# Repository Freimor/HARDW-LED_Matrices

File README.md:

## Stack of different led modular matrices.
I make modular matrices on different LEDs in the same form factor. Trying to make the smallest 8x8 matrix.

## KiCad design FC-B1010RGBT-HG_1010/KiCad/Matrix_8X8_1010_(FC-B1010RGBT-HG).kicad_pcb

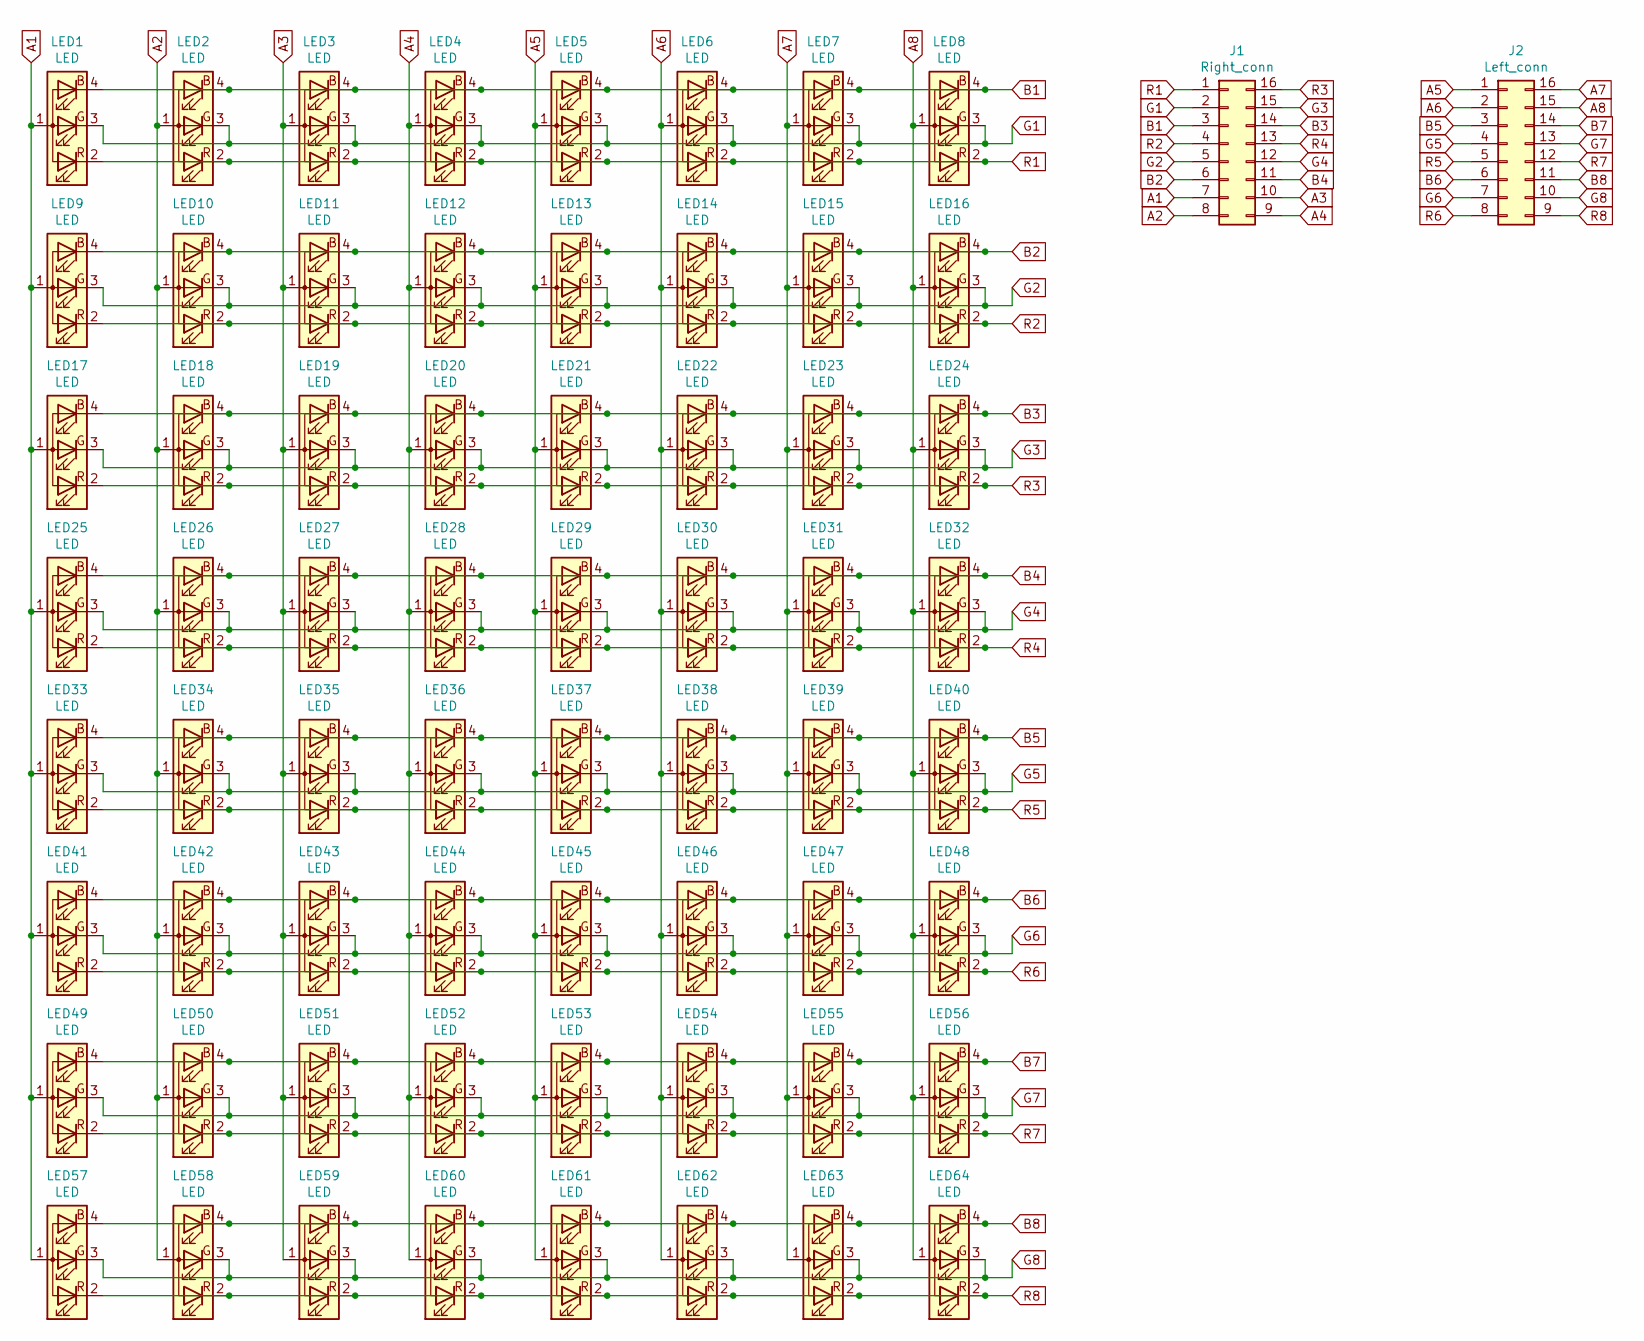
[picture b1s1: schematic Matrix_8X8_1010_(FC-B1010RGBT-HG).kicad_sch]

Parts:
J1: Right_conn; Conn_Molex_5050701642(SlimStack_16pin_header)
J2: Left_conn; Conn_Molex_5050701642(SlimStack_16pin_header)
LED1, LED2, LED3, LED4, LED5, LED6, LED7, LED8, LED9, LED10, LED11, LED12, LED13, LED14, LED15, LED16, LED17, LED18, LED19, LED20, LED21, LED22, LED23, LED24, LED25, LED26, LED27, LED28, LED29, LED30, LED31, LED32, LED33, LED34, LED35, LED36, LED37, LED38, LED39, LED40, LED41, LED42, LED43, LED44, LED45, LED46, LED47, LED48, LED49, LED50, LED51, LED52, LED53, LED54, LED55, LED56, LED57, LED58, LED59, LED60, LED61, LED62, LED63, LED64: LED; LED_RGB_FC-B1010RGBT-HG

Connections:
A1: J1.7, LED1.1 (A), LED9.1 (A), LED17.1 (A), LED25.1 (A), LED33.1 (A), LED41.1 (A), LED49.1 (A), LED57.1 (A)
A2: J1.8, LED2.1 (A), LED10.1 (A), LED18.1 (A), LED26.1 (A), LED34.1 (A), LED42.1 (A), LED50.1 (A), LED58.1 (A)
A3: J1.10, LED3.1 (A), LED11.1 (A), LED19.1 (A), LED27.1 (A), LED35.1 (A), LED43.1 (A), LED51.1 (A), LED59.1 (A)
A4: J1.9, LED4.1 (A), LED12.1 (A), LED20.1 (A), LED28.1 (A), LED36.1 (A), LED44.1 (A), LED52.1 (A), LED60.1 (A)
A5: J2.1, LED5.1 (A), LED13.1 (A), LED21.1 (A), LED29.1 (A), LED37.1 (A), LED45.1 (A), LED53.1 (A), LED61.1 (A)
A6: J2.2, LED6.1 (A), LED14.1 (A), LED22.1 (A), LED30.1 (A), LED38.1 (A), LED46.1 (A), LED54.1 (A), LED62.1 (A)
A7: J2.16, LED7.1 (A), LED15.1 (A), LED23.1 (A), LED31.1 (A), LED39.1 (A), LED47.1 (A), LED55.1 (A), LED63.1 (A)
A8: J2.15, LED8.1 (A), LED16.1 (A), LED24.1 (A), LED32.1 (A), LED40.1 (A), LED48.1 (A), LED56.1 (A), LED64.1 (A)
B1: J1.3, LED1.4 (BK), LED2.4 (BK), LED3.4 (BK), LED4.4 (BK), LED5.4 (BK), LED6.4 (BK), LED7.4 (BK), LED8.4 (BK)
B2: J1.6, LED9.4 (BK), LED10.4 (BK), LED11.4 (BK), LED12.4 (BK), LED13.4 (BK), LED14.4 (BK), LED15.4 (BK), LED16.4 (BK)
B3: J1.14, LED17.4 (BK), LED18.4 (BK), LED19.4 (BK), LED20.4 (BK), LED21.4 (BK), LED22.4 (BK), LED23.4 (BK), LED24.4 (BK)
B4: J1.11, LED25.4 (BK), LED26.4 (BK), LED27.4 (BK), LED28.4 (BK), LED29.4 (BK), LED30.4 (BK), LED31.4 (BK), LED32.4 (BK)
B5: J2.3, LED33.4 (BK), LED34.4 (BK), LED35.4 (BK), LED36.4 (BK), LED37.4 (BK), LED38.4 (BK), LED39.4 (BK), LED40.4 (BK)
B6: J2.6, LED41.4 (BK), LED42.4 (BK), LED43.4 (BK), LED44.4 (BK), LED45.4 (BK), LED46.4 (BK), LED47.4 (BK), LED48.4 (BK)
B7: J2.14, LED49.4 (BK), LED50.4 (BK), LED51.4 (BK), LED52.4 (BK), LED53.4 (BK), LED54.4 (BK), LED55.4 (BK), LED56.4 (BK)
B8: J2.11, LED57.4 (BK), LED58.4 (BK), LED59.4 (BK), LED60.4 (BK), LED61.4 (BK), LED62.4 (BK), LED63.4 (BK), LED64.4 (BK)
G1: J1.2, LED1.3 (GK), LED2.3 (GK), LED3.3 (GK), LED4.3 (GK), LED5.3 (GK), LED6.3 (GK), LED7.3 (GK), LED8.3 (GK)
G2: J1.5, LED9.3 (GK), LED10.3 (GK), LED11.3 (GK), LED12.3 (GK), LED13.3 (GK), LED14.3 (GK), LED15.3 (GK), LED16.3 (GK)
G3: J1.15, LED17.3 (GK), LED18.3 (GK), LED19.3 (GK), LED20.3 (GK), LED21.3 (GK), LED22.3 (GK), LED23.3 (GK), LED24.3 (GK)
G4: J1.12, LED25.3 (GK), LED26.3 (GK), LED27.3 (GK), LED28.3 (GK), LED29.3 (GK), LED30.3 (GK), LED31.3 (GK), LED32.3 (GK)
G5: J2.4, LED33.3 (GK), LED34.3 (GK), LED35.3 (GK), LED36.3 (GK), LED37.3 (GK), LED38.3 (GK), LED39.3 (GK), LED40.3 (GK)
G6: J2.7, LED41.3 (GK), LED42.3 (GK), LED43.3 (GK), LED44.3 (GK), LED45.3 (GK), LED46.3 (GK), LED47.3 (GK), LED48.3 (GK)
G7: J2.13, LED49.3 (GK), LED50.3 (GK), LED51.3 (GK), LED52.3 (GK), LED53.3 (GK), LED54.3 (GK), LED55.3 (GK), LED56.3 (GK)
G8: J2.10, LED57.3 (GK), LED58.3 (GK), LED59.3 (GK), LED60.3 (GK), LED61.3 (GK), LED62.3 (GK), LED63.3 (GK), LED64.3 (GK)
R1: J1.1, LED1.2 (RK), LED2.2 (RK), LED3.2 (RK), LED4.2 (RK), LED5.2 (RK), LED6.2 (RK), LED7.2 (RK), LED8.2 (RK)
R2: J1.4, LED9.2 (RK), LED10.2 (RK), LED11.2 (RK), LED12.2 (RK), LED13.2 (RK), LED14.2 (RK), LED15.2 (RK), LED16.2 (RK)
R3: J1.16, LED17.2 (RK), LED18.2 (RK), LED19.2 (RK), LED20.2 (RK), LED21.2 (RK), LED22.2 (RK), LED23.2 (RK), LED24.2 (RK)
R4: J1.13, LED25.2 (RK), LED26.2 (RK), LED27.2 (RK), LED28.2 (RK), LED29.2 (RK), LED30.2 (RK), LED31.2 (RK), LED32.2 (RK)
R5: J2.5, LED33.2 (RK), LED34.2 (RK), LED35.2 (RK), LED36.2 (RK), LED37.2 (RK), LED38.2 (RK), LED39.2 (RK), LED40.2 (RK)
R6: J2.8, LED41.2 (RK), LED42.2 (RK), LED43.2 (RK), LED44.2 (RK), LED45.2 (RK), LED46.2 (RK), LED47.2 (RK), LED48.2 (RK)
R7: J2.12, LED49.2 (RK), LED50.2 (RK), LED51.2 (RK), LED52.2 (RK), LED53.2 (RK), LED54.2 (RK), LED55.2 (RK), LED56.2 (RK)
R8: J2.9, LED57.2 (RK), LED58.2 (RK), LED59.2 (RK), LED60.2 (RK), LED61.2 (RK), LED62.2 (RK), LED63.2 (RK), LED64.2 (RK)

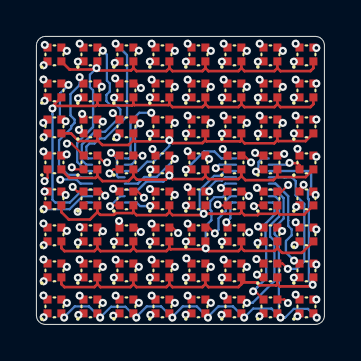
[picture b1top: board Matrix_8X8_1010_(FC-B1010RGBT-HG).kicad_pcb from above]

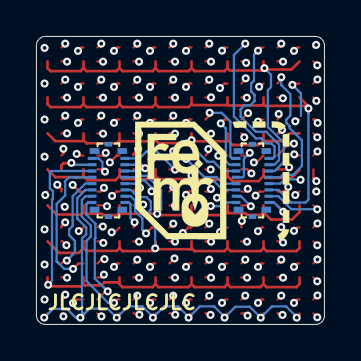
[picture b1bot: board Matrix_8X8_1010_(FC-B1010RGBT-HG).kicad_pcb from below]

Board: 4 copper layers, 16.0 x 16.0 mm, 67 parts (2 on the bottom side), 32 nets.

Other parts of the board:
Ref**: Val**; drawing

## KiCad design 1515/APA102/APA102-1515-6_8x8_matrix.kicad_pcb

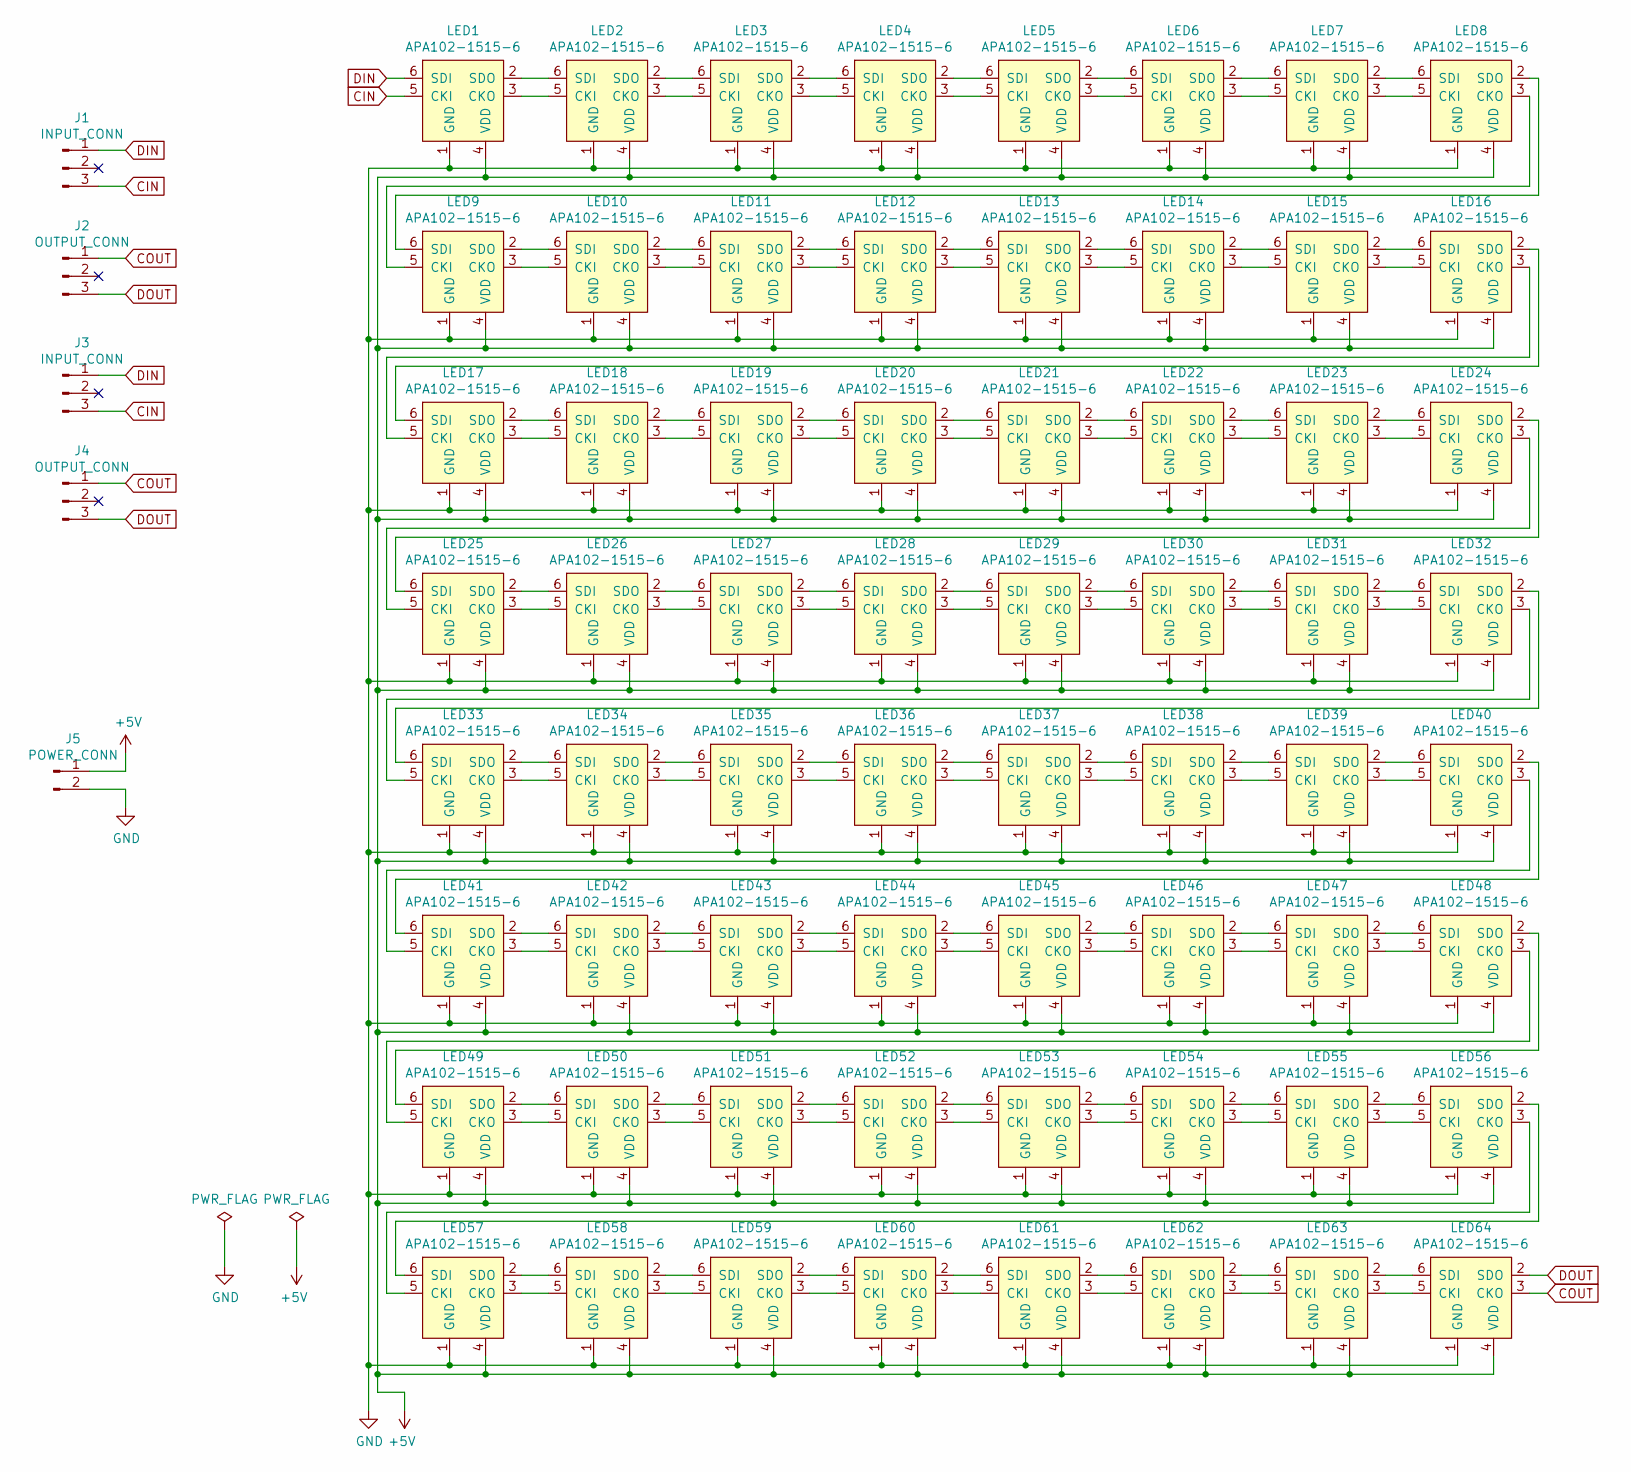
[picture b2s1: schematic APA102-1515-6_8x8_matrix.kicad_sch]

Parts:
J1, J3: INPUT_CONN; Conn_Hirose_DF59-3S-2V
J2, J4: OUTPUT_CONN; Conn_Hirose_DF59-3S-2V
J5: POWER_CONN; Conn_Molex_2026560021(Pico-EZmate_Slim)
LED1, LED2, LED3, LED4, LED5, LED6, LED7, LED8, LED9, LED10, LED11, LED12, LED13, LED14, LED15, LED16, LED17, LED18, LED19, LED20, LED21, LED22, LED23, LED24, LED25, LED26, LED27, LED28, LED29, LED30, LED31, LED32, LED33, LED34, LED35, LED36, LED37, LED38, LED39, LED40, LED41, LED42, LED43, LED44, LED45, LED46, LED47, LED48, LED49, LED50, LED51, LED52, LED53, LED54, LED55, LED56, LED57, LED58, LED59, LED60, LED61, LED62, LED63, LED64: APA102-1515-6

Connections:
+5V: J5.1, LED1.4 (VDD), LED2.4 (VDD), LED3.4 (VDD), LED4.4 (VDD), LED5.4 (VDD), LED6.4 (VDD), LED7.4 (VDD), LED8.4 (VDD), LED9.4 (VDD), LED10.4 (VDD), LED11.4 (VDD), LED12.4 (VDD), LED13.4 (VDD), LED14.4 (VDD), LED15.4 (VDD), LED16.4 (VDD), LED17.4 (VDD), LED18.4 (VDD), LED19.4 (VDD), LED20.4 (VDD), LED21.4 (VDD), LED22.4 (VDD), LED23.4 (VDD), LED24.4 (VDD), LED25.4 (VDD), LED26.4 (VDD), LED27.4 (VDD), LED28.4 (VDD), LED29.4 (VDD), LED30.4 (VDD), LED31.4 (VDD), LED32.4 (VDD), LED33.4 (VDD), LED34.4 (VDD), LED35.4 (VDD), LED36.4 (VDD), LED37.4 (VDD), LED38.4 (VDD), LED39.4 (VDD), LED40.4 (VDD), LED41.4 (VDD), LED42.4 (VDD), LED43.4 (VDD), LED44.4 (VDD), LED45.4 (VDD), LED46.4 (VDD), LED47.4 (VDD), LED48.4 (VDD), LED49.4 (VDD), LED50.4 (VDD), LED51.4 (VDD), LED52.4 (VDD), LED53.4 (VDD), LED54.4 (VDD), LED55.4 (VDD), LED56.4 (VDD), LED57.4 (VDD), LED58.4 (VDD), LED59.4 (VDD), LED60.4 (VDD), LED61.4 (VDD), LED62.4 (VDD), LED63.4 (VDD), LED64.4 (VDD)
CIN: J1.3, J3.3, LED1.5 (CKI)
COUT: J2.1, J4.1, LED64.3 (CKO)
DIN: J1.1, J3.1, LED1.6 (SDI)
DOUT: J2.3, J4.3, LED64.2 (SDO)
GND: J5.2, LED1.1 (GND), LED2.1 (GND), LED3.1 (GND), LED4.1 (GND), LED5.1 (GND), LED6.1 (GND), LED7.1 (GND), LED8.1 (GND), LED9.1 (GND), LED10.1 (GND), LED11.1 (GND), LED12.1 (GND), LED13.1 (GND), LED14.1 (GND), LED15.1 (GND), LED16.1 (GND), LED17.1 (GND), LED18.1 (GND), LED19.1 (GND), LED20.1 (GND), LED21.1 (GND), LED22.1 (GND), LED23.1 (GND), LED24.1 (GND), LED25.1 (GND), LED26.1 (GND), LED27.1 (GND), LED28.1 (GND), LED29.1 (GND), LED30.1 (GND), LED31.1 (GND), LED32.1 (GND), LED33.1 (GND), LED34.1 (GND), LED35.1 (GND), LED36.1 (GND), LED37.1 (GND), LED38.1 (GND), LED39.1 (GND), LED40.1 (GND), LED41.1 (GND), LED42.1 (GND), LED43.1 (GND), LED44.1 (GND), LED45.1 (GND), LED46.1 (GND), LED47.1 (GND), LED48.1 (GND), LED49.1 (GND), LED50.1 (GND), LED51.1 (GND), LED52.1 (GND), LED53.1 (GND), LED54.1 (GND), LED55.1 (GND), LED56.1 (GND), LED57.1 (GND), LED58.1 (GND), LED59.1 (GND), LED60.1 (GND), LED61.1 (GND), LED62.1 (GND), LED63.1 (GND), LED64.1 (GND)
unnamed: LED1.2 (SDO), LED2.6 (SDI)
unnamed: LED1.3 (CKO), LED2.5 (CKI)
unnamed: LED2.2 (SDO), LED3.6 (SDI)
unnamed: LED2.3 (CKO), LED3.5 (CKI)
unnamed: LED3.2 (SDO), LED4.6 (SDI)
unnamed: LED3.3 (CKO), LED4.5 (CKI)
unnamed: LED4.2 (SDO), LED5.6 (SDI)
unnamed: LED4.3 (CKO), LED5.5 (CKI)
unnamed: LED5.2 (SDO), LED6.6 (SDI)
unnamed: LED5.3 (CKO), LED6.5 (CKI)
unnamed: LED6.2 (SDO), LED7.6 (SDI)
unnamed: LED6.3 (CKO), LED7.5 (CKI)
unnamed: LED7.2 (SDO), LED8.6 (SDI)
unnamed: LED7.3 (CKO), LED8.5 (CKI)
unnamed: LED8.2 (SDO), LED9.6 (SDI)
unnamed: LED8.3 (CKO), LED9.5 (CKI)
unnamed: LED10.2 (SDO), LED11.6 (SDI)
unnamed: LED10.3 (CKO), LED11.5 (CKI)
unnamed: LED9.3 (CKO), LED10.5 (CKI)
unnamed: LED9.2 (SDO), LED10.6 (SDI)
unnamed: LED11.2 (SDO), LED12.6 (SDI)
unnamed: LED11.3 (CKO), LED12.5 (CKI)
unnamed: LED12.2 (SDO), LED13.6 (SDI)
unnamed: LED12.3 (CKO), LED13.5 (CKI)
unnamed: LED13.2 (SDO), LED14.6 (SDI)
unnamed: LED13.3 (CKO), LED14.5 (CKI)
unnamed: LED14.2 (SDO), LED15.6 (SDI)
unnamed: LED14.3 (CKO), LED15.5 (CKI)
unnamed: LED15.2 (SDO), LED16.6 (SDI)
unnamed: LED15.3 (CKO), LED16.5 (CKI)
unnamed: LED16.2 (SDO), LED17.6 (SDI)
unnamed: LED16.3 (CKO), LED17.5 (CKI)
unnamed: LED17.2 (SDO), LED18.6 (SDI)
unnamed: LED17.3 (CKO), LED18.5 (CKI)
unnamed: LED18.2 (SDO), LED19.6 (SDI)
unnamed: LED18.3 (CKO), LED19.5 (CKI)
unnamed: LED19.2 (SDO), LED20.6 (SDI)
unnamed: LED19.3 (CKO), LED20.5 (CKI)
unnamed: LED20.2 (SDO), LED21.6 (SDI)
unnamed: LED20.3 (CKO), LED21.5 (CKI)
unnamed: LED21.2 (SDO), LED22.6 (SDI)
unnamed: LED21.3 (CKO), LED22.5 (CKI)
unnamed: LED22.2 (SDO), LED23.6 (SDI)
unnamed: LED22.3 (CKO), LED23.5 (CKI)
unnamed: LED23.2 (SDO), LED24.6 (SDI)
unnamed: LED23.3 (CKO), LED24.5 (CKI)
unnamed: LED24.2 (SDO), LED25.6 (SDI)
unnamed: LED24.3 (CKO), LED25.5 (CKI)
unnamed: LED25.2 (SDO), LED26.6 (SDI)
unnamed: LED25.3 (CKO), LED26.5 (CKI)
unnamed: LED26.2 (SDO), LED27.6 (SDI)
unnamed: LED26.3 (CKO), LED27.5 (CKI)
unnamed: LED27.2 (SDO), LED28.6 (SDI)
unnamed: LED27.3 (CKO), LED28.5 (CKI)
unnamed: LED28.2 (SDO), LED29.6 (SDI)
unnamed: LED28.3 (CKO), LED29.5 (CKI)
unnamed: LED29.2 (SDO), LED30.6 (SDI)
unnamed: LED29.3 (CKO), LED30.5 (CKI)
unnamed: LED30.2 (SDO), LED31.6 (SDI)
unnamed: LED30.3 (CKO), LED31.5 (CKI)
unnamed: LED31.2 (SDO), LED32.6 (SDI)
unnamed: LED31.3 (CKO), LED32.5 (CKI)
unnamed: LED32.2 (SDO), LED33.6 (SDI)
unnamed: LED32.3 (CKO), LED33.5 (CKI)
unnamed: LED33.2 (SDO), LED34.6 (SDI)
unnamed: LED33.3 (CKO), LED34.5 (CKI)
unnamed: LED34.2 (SDO), LED35.6 (SDI)
unnamed: LED34.3 (CKO), LED35.5 (CKI)
unnamed: LED35.2 (SDO), LED36.6 (SDI)
unnamed: LED35.3 (CKO), LED36.5 (CKI)
unnamed: LED36.2 (SDO), LED37.6 (SDI)
unnamed: LED36.3 (CKO), LED37.5 (CKI)
unnamed: LED37.2 (SDO), LED38.6 (SDI)
unnamed: LED37.3 (CKO), LED38.5 (CKI)
unnamed: LED38.2 (SDO), LED39.6 (SDI)
unnamed: LED38.3 (CKO), LED39.5 (CKI)
unnamed: LED39.2 (SDO), LED40.6 (SDI)
unnamed: LED39.3 (CKO), LED40.5 (CKI)
unnamed: LED40.2 (SDO), LED41.6 (SDI)
unnamed: LED40.3 (CKO), LED41.5 (CKI)
unnamed: LED41.2 (SDO), LED42.6 (SDI)
unnamed: LED41.3 (CKO), LED42.5 (CKI)
unnamed: LED42.2 (SDO), LED43.6 (SDI)
unnamed: LED42.3 (CKO), LED43.5 (CKI)
unnamed: LED43.2 (SDO), LED44.6 (SDI)
unnamed: LED43.3 (CKO), LED44.5 (CKI)
unnamed: LED44.2 (SDO), LED45.6 (SDI)
unnamed: LED44.3 (CKO), LED45.5 (CKI)
unnamed: LED45.2 (SDO), LED46.6 (SDI)
unnamed: LED45.3 (CKO), LED46.5 (CKI)
unnamed: LED46.2 (SDO), LED47.6 (SDI)
unnamed: LED46.3 (CKO), LED47.5 (CKI)
unnamed: LED47.2 (SDO), LED48.6 (SDI)
unnamed: LED47.3 (CKO), LED48.5 (CKI)
unnamed: LED48.2 (SDO), LED49.6 (SDI)
unnamed: LED48.3 (CKO), LED49.5 (CKI)
unnamed: LED49.2 (SDO), LED50.6 (SDI)
unnamed: LED49.3 (CKO), LED50.5 (CKI)
unnamed: LED50.2 (SDO), LED51.6 (SDI)
unnamed: LED50.3 (CKO), LED51.5 (CKI)
unnamed: LED51.2 (SDO), LED52.6 (SDI)
unnamed: LED51.3 (CKO), LED52.5 (CKI)
unnamed: LED52.2 (SDO), LED53.6 (SDI)
unnamed: LED52.3 (CKO), LED53.5 (CKI)
unnamed: LED53.2 (SDO), LED54.6 (SDI)
unnamed: LED53.3 (CKO), LED54.5 (CKI)
unnamed: LED54.2 (SDO), LED55.6 (SDI)
unnamed: LED54.3 (CKO), LED55.5 (CKI)
unnamed: LED55.2 (SDO), LED56.6 (SDI)
unnamed: LED55.3 (CKO), LED56.5 (CKI)
unnamed: LED56.2 (SDO), LED57.6 (SDI)
unnamed: LED56.3 (CKO), LED57.5 (CKI)
unnamed: LED57.2 (SDO), LED58.6 (SDI)
unnamed: LED57.3 (CKO), LED58.5 (CKI)
unnamed: LED58.2 (SDO), LED59.6 (SDI)
unnamed: LED58.3 (CKO), LED59.5 (CKI)
unnamed: LED59.2 (SDO), LED60.6 (SDI)
unnamed: LED59.3 (CKO), LED60.5 (CKI)
unnamed: LED60.2 (SDO), LED61.6 (SDI)
unnamed: LED60.3 (CKO), LED61.5 (CKI)
unnamed: LED61.2 (SDO), LED62.6 (SDI)
unnamed: LED61.3 (CKO), LED62.5 (CKI)
unnamed: LED62.2 (SDO), LED63.6 (SDI)
unnamed: LED62.3 (CKO), LED63.5 (CKI)
unnamed: LED63.2 (SDO), LED64.6 (SDI)
unnamed: LED63.3 (CKO), LED64.5 (CKI)

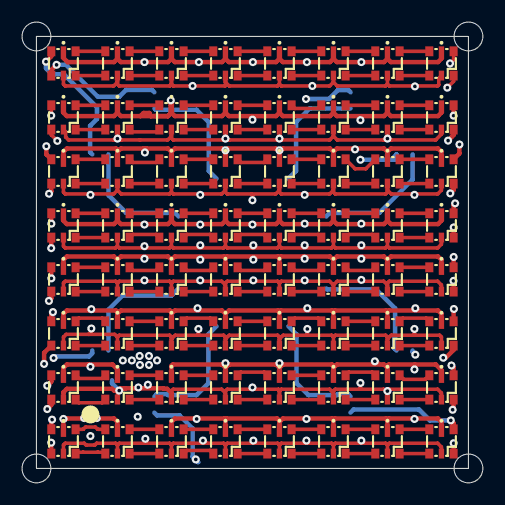
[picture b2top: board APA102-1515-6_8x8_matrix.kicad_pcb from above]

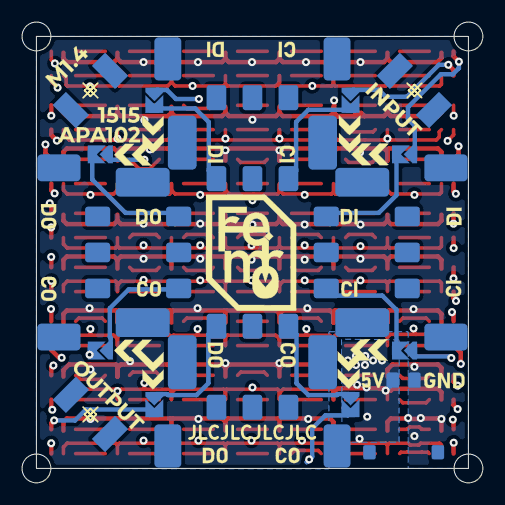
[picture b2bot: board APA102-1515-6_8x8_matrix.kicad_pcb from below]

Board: 4 copper layers, 24.0 x 24.0 mm, 69 parts (5 on the bottom side), 132 nets.

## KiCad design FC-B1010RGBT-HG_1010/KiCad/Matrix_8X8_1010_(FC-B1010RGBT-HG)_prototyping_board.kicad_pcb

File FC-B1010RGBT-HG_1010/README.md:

## FC-B1010RGBT-HG Matrix
 
## FC-B1010RGBT-HG driver board

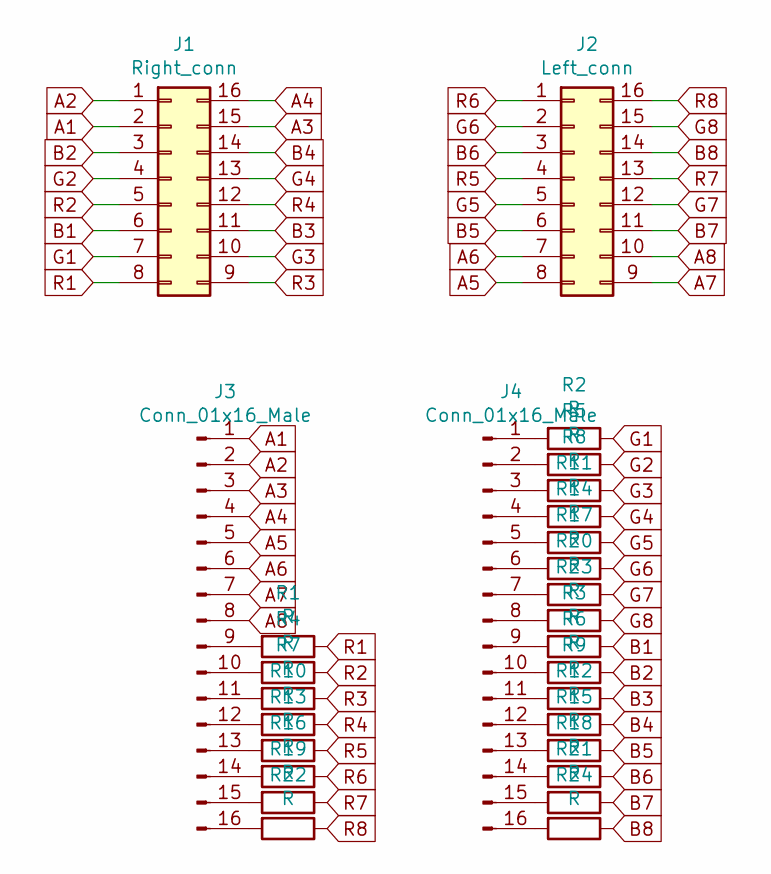
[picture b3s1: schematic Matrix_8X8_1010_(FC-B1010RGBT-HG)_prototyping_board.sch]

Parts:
J1: Right_conn; Conn_Molex_5050661622(SlimStack_16pin_receptable)
J2: Left_conn; Conn_Molex_5050661622(SlimStack_16pin_receptable)
J3, J4: Conn_01x16_Male; PinHeader_1x16_P2.54mm_Vertical
R1, R2, R3, R4, R5, R6, R7, R8, R9, R10, R11, R12, R13, R14, R15, R16, R17, R18, R19, R20, R21, R22, R23, R24: R; R_0402_1005Metric_Pad0.72x0.64mm_HandSolder

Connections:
A1: J1.2, J3.1
A2: J1.1, J3.2
A3: J1.15, J3.3
A4: J1.16, J3.4
A5: J2.8, J3.5
A6: J2.7, J3.6
A7: J2.9, J3.7
A8: J2.10, J3.8
B1: J1.6, R3.1
B2: J1.3, R6.1
B3: J1.11, R9.1
B4: J1.14, R12.1
B5: J2.6, R15.1
B6: J2.3, R18.1
B7: J2.11, R21.1
B8: J2.14, R24.1
G1: J1.7, R2.1
G2: J1.4, R5.1
G3: J1.10, R8.1
G4: J1.13, R11.1
G5: J2.5, R14.1
G6: J2.2, R17.1
G7: J2.12, R20.1
G8: J2.15, R23.1
unnamed: J3.9, R1.2
unnamed: J3.10, R4.2
unnamed: J3.11, R7.2
unnamed: J3.12, R10.2
unnamed: J3.13, R13.2
unnamed: J3.14, R16.2
unnamed: J3.15, R19.2
unnamed: J3.16, R22.2
unnamed: J4.1, R2.2
unnamed: J4.2, R5.2
unnamed: J4.3, R8.2
unnamed: J4.4, R11.2
unnamed: J4.5, R14.2
unnamed: J4.6, R17.2
unnamed: J4.7, R20.2
unnamed: J4.8, R23.2
unnamed: J4.9, R3.2
unnamed: J4.10, R6.2
unnamed: J4.11, R9.2
unnamed: J4.12, R12.2
unnamed: J4.13, R15.2
unnamed: J4.14, R18.2
unnamed: J4.15, R21.2
unnamed: J4.16, R24.2
R1: J1.8, R1.1
R2: J1.5, R4.1
R3: J1.9, R7.1
R4: J1.12, R10.1
R5: J2.4, R13.1
R6: J2.1, R16.1
R7: J2.13, R19.1
R8: J2.16, R22.1

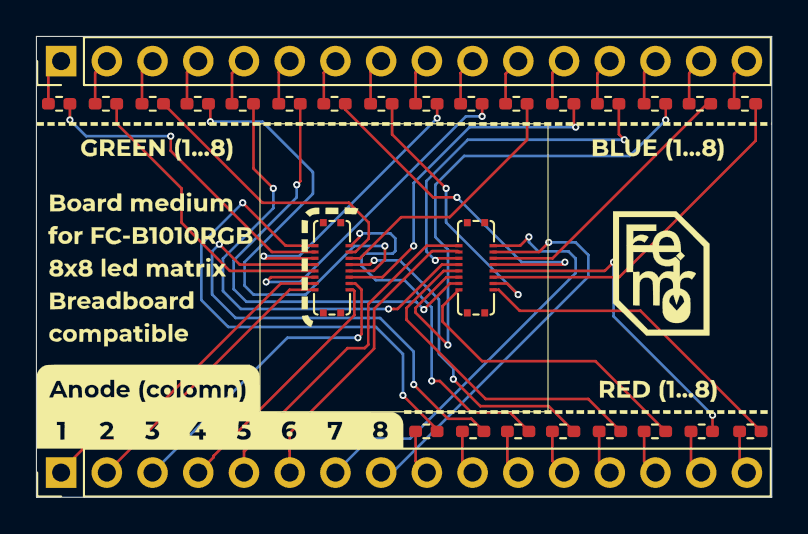
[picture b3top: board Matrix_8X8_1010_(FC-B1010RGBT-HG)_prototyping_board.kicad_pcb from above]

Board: 2 copper layers, 40.9 x 25.6 mm, 29 parts (0 on the bottom side), 56 nets.

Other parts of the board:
Ref**: Val**; Proto_silk

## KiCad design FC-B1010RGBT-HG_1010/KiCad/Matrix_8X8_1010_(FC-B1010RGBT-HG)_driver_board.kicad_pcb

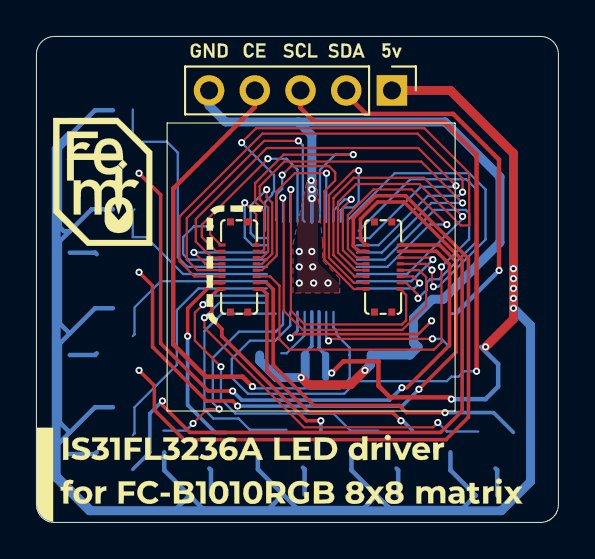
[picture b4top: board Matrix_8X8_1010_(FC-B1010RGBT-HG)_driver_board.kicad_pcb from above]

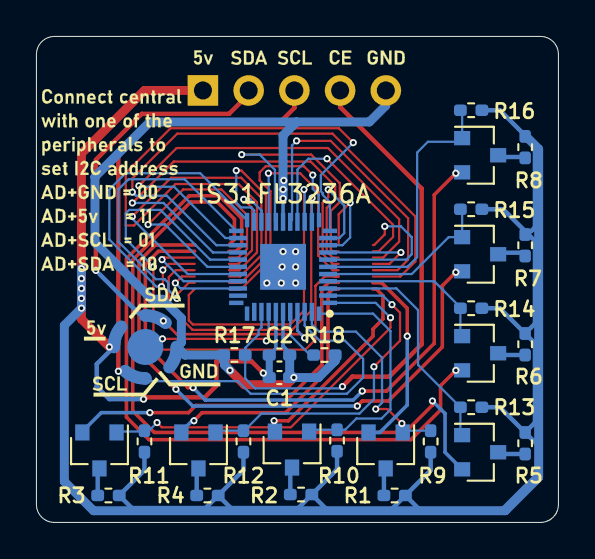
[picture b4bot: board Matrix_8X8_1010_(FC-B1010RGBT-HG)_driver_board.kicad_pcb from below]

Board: 2 copper layers, 29.0 x 27.0 mm, 36 parts (30 on the bottom side), 55 nets.

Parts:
C1: 1uF; C_0402_1005Metric_Pad0.74x0.62mm_HandSolder
C2: 100nF; C_0402_1005Metric_Pad0.74x0.62mm_HandSolder
IS31FL3236A: IS31FL3236A; IS31FL3236A_(QFN-44)
J1: Right_conn; Conn_Molex_5050661622(SlimStack_16pin_receptable)
J2: Left_conn; Conn_Molex_5050661622(SlimStack_16pin_receptable)
J3: Conn_01x05_Male; PinHeader_1x05_P2.54mm_Vertical
JP1: SolderJumper_4_Open; SolderJumper-4
Q1, Q2, Q3, Q4, Q5, Q6, Q7, Q8: S8550(SOT-23); SOT-23
R1, R2, R3, R4, R5, R6, R7, R8: 22; R_0402_1005Metric_Pad0.72x0.64mm_HandSolder
R9, R10, R11, R12, R13, R14, R15, R16, R17: 10k; R_0402_1005Metric_Pad0.72x0.64mm_HandSolder
R18: 7,68k; R_0402_1005Metric_Pad0.72x0.64mm_HandSolder
Ref**: Val**; Driver_board_back_silk
Ref**#2: Val**; Driver_board_front_silk
Ref**#3: Val**; Key_front

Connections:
A1: J1.2, Q1.2
A2: J1.1, Q2.2
A3: J1.15, Q3.2
A4: J1.16, Q4.2
A5: J2.8, Q5.2
A6: J2.7, Q6.2
A7: J2.9, Q7.2
A8: J2.10, Q8.2
AD: IS31FL3236A.37, JP1.1
B1: IS31FL3236A.24, J1.6
B2: IS31FL3236A.25, J1.3
B3: IS31FL3236A.26, J1.11
B4: IS31FL3236A.27, J1.14
B5: IS31FL3236A.28, J2.6
B6: IS31FL3236A.29, J2.3
B7: IS31FL3236A.30, J2.11
B8: IS31FL3236A.31, J2.14
G1: IS31FL3236A.15, J1.7
G2: IS31FL3236A.16, J1.4
G3: IS31FL3236A.18, J1.10
G4: IS31FL3236A.19, J1.13
G5: IS31FL3236A.20, J2.5
G6: IS31FL3236A.21, J2.2
G7: IS31FL3236A.22, J2.12
G8: IS31FL3236A.23, J2.15
GND: C1.2, C2.2, IS31FL3236A.0, IS31FL3236A.17, IS31FL3236A.39, J3.5, JP1.4, R17.2, R18.2
unnamed: IS31FL3236A.43, Q1.1, R9.2
unnamed: Q1.3, R1.2
unnamed: IS31FL3236A.44, Q2.1, R10.2
unnamed: Q2.3, R2.2
unnamed: IS31FL3236A.1, Q3.1, R11.2
unnamed: Q3.3, R3.2
unnamed: IS31FL3236A.2, Q4.1, R12.2
unnamed: Q4.3, R4.2
unnamed: IS31FL3236A.3, Q5.1, R13.2
unnamed: Q5.3, R5.2
unnamed: IS31FL3236A.4, Q6.1, R14.2
unnamed: Q6.3, R6.2
unnamed: IS31FL3236A.5, Q7.1, R15.2
unnamed: Q7.3, R7.2
unnamed: IS31FL3236A.6, Q8.1, R16.2
unnamed: Q8.3, R8.2
unnamed: IS31FL3236A.40, R18.1
R1: IS31FL3236A.7, J1.8
R2: IS31FL3236A.8, J1.5
R3: IS31FL3236A.9, J1.9
R4: IS31FL3236A.10, J1.12
R5: IS31FL3236A.11, J2.4
R6: IS31FL3236A.12, J2.1
R7: IS31FL3236A.13, J2.13
R8: IS31FL3236A.14, J2.16
SCL: IS31FL3236A.42, J3.3, JP1.3
SDA: IS31FL3236A.41, J3.2, JP1.5
SDB: IS31FL3236A.36, J3.4, R17.1
VCC: C1.1, C2.1, IS31FL3236A.38, J3.1, JP1.2, R1.1, R2.1, R3.1, R4.1, R5.1, R6.1, R7.1, R8.1, R9.1, R10.1, R11.1, R12.1, R13.1, R14.1, R15.1, R16.1

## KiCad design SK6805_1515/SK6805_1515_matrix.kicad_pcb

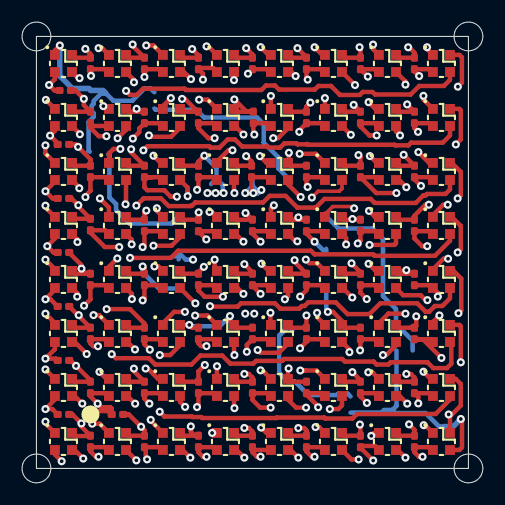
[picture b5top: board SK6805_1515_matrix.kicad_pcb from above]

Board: 4 copper layers, 24.0 x 24.0 mm, 64 parts (0 on the bottom side), 65 nets.

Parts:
LED1, LED2, LED3, LED4, LED5, LED6, LED7, LED8, LED9, LED10, LED11, LED12, LED13, LED14, LED15, LED16, LED17, LED18, LED19, LED20, LED21, LED22, LED23, LED24, LED25, LED26, LED27, LED28, LED29, LED30, LED31, LED32, LED33, LED34, LED35, LED36, LED37, LED38, LED39, LED40, LED41, LED42, LED43, LED44, LED45, LED46, LED47, LED48, LED49, LED50, LED51, LED52, LED53, LED54, LED55, LED56, LED57, LED58, LED59, LED60, LED61, LED62, LED63, LED64: SK6805-EC15

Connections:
+5V: LED1.2, LED2.2, LED3.2, LED4.2, LED5.2, LED6.2, LED7.2, LED8.2, LED9.2, LED10.2, LED11.2, LED12.2, LED13.2, LED14.2, LED15.2, LED16.2, LED17.2, LED18.2, LED19.2, LED20.2, LED21.2, LED22.2, LED23.2, LED24.2, LED25.2, LED26.2, LED27.2, LED28.2, LED29.2, LED30.2, LED31.2, LED32.2, LED33.2, LED34.2, LED35.2, LED36.2, LED37.2, LED38.2, LED39.2, LED40.2, LED41.2, LED42.2, LED43.2, LED44.2, LED45.2, LED46.2, LED47.2, LED48.2, LED49.2, LED50.2, LED51.2, LED52.2, LED53.2, LED54.2, LED55.2, LED56.2, LED57.2, LED58.2, LED59.2, LED60.2, LED61.2, LED62.2, LED63.2, LED64.2
GND: LED1.4, LED2.4, LED3.4, LED4.4, LED5.4, LED6.4, LED7.4, LED8.4, LED9.4, LED10.4, LED11.4, LED12.4, LED13.4, LED14.4, LED15.4, LED16.4, LED17.4, LED18.4, LED19.4, LED20.4, LED21.4, LED22.4, LED23.4, LED24.4, LED25.4, LED26.4, LED27.4, LED28.4, LED29.4, LED30.4, LED31.4, LED32.4, LED33.4, LED34.4, LED35.4, LED36.4, LED37.4, LED38.4, LED39.4, LED40.4, LED41.4, LED42.4, LED43.4, LED44.4, LED45.4, LED46.4, LED47.4, LED48.4, LED49.4, LED50.4, LED51.4, LED52.4, LED53.4, LED54.4, LED55.4, LED56.4, LED57.4, LED58.4, LED59.4, LED60.4, LED61.4, LED62.4, LED63.4, LED64.4
unnamed: LED1.3, LED2.1
unnamed: LED2.3, LED3.1
unnamed: LED3.3, LED4.1
unnamed: LED4.3, LED5.1
unnamed: LED5.3, LED6.1
unnamed: LED6.3, LED7.1
unnamed: LED7.3, LED8.1
unnamed: LED8.3, LED9.1
unnamed: LED9.3, LED10.1
unnamed: LED10.3, LED11.1
unnamed: LED11.3, LED12.1
unnamed: LED12.3, LED13.1
unnamed: LED13.3, LED14.1
unnamed: LED14.3, LED15.1
unnamed: LED15.3, LED16.1
unnamed: LED16.3, LED17.1
unnamed: LED17.3, LED18.1
unnamed: LED18.3, LED19.1
unnamed: LED19.3, LED20.1
unnamed: LED20.3, LED21.1
unnamed: LED21.3, LED22.1
unnamed: LED22.3, LED23.1
unnamed: LED23.3, LED24.1
unnamed: LED24.3, LED25.1
unnamed: LED25.3, LED26.1
unnamed: LED26.3, LED27.1
unnamed: LED27.3, LED28.1
unnamed: LED28.3, LED29.1
unnamed: LED29.3, LED30.1
unnamed: LED30.3, LED31.1
unnamed: LED31.3, LED32.1
unnamed: LED32.3, LED33.1
unnamed: LED33.3, LED34.1
unnamed: LED34.3, LED35.1
unnamed: LED35.3, LED36.1
unnamed: LED36.3, LED37.1
unnamed: LED37.3, LED38.1
unnamed: LED38.3, LED39.1
unnamed: LED39.3, LED40.1
unnamed: LED40.3, LED41.1
unnamed: LED41.3, LED42.1
unnamed: LED42.3, LED43.1
unnamed: LED43.3, LED44.1
unnamed: LED44.3, LED45.1
unnamed: LED45.3, LED46.1
unnamed: LED46.3, LED47.1
unnamed: LED47.3, LED48.1
unnamed: LED48.3, LED49.1
unnamed: LED49.3, LED50.1
unnamed: LED50.3, LED51.1
unnamed: LED51.3, LED52.1
unnamed: LED52.3, LED53.1
unnamed: LED53.3, LED54.1
unnamed: LED54.3, LED55.1
unnamed: LED55.3, LED56.1
unnamed: LED56.3, LED57.1
unnamed: LED57.3, LED58.1
unnamed: LED58.3, LED59.1
unnamed: LED59.3, LED60.1
unnamed: LED60.3, LED61.1
unnamed: LED61.3, LED62.1
unnamed: LED62.3, LED63.1
unnamed: LED63.3, LED64.1

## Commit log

2022-10-01 Initial update
2022-10-01 Add APA102 and SK6805
2022-10-04 Add 1010 matrix
